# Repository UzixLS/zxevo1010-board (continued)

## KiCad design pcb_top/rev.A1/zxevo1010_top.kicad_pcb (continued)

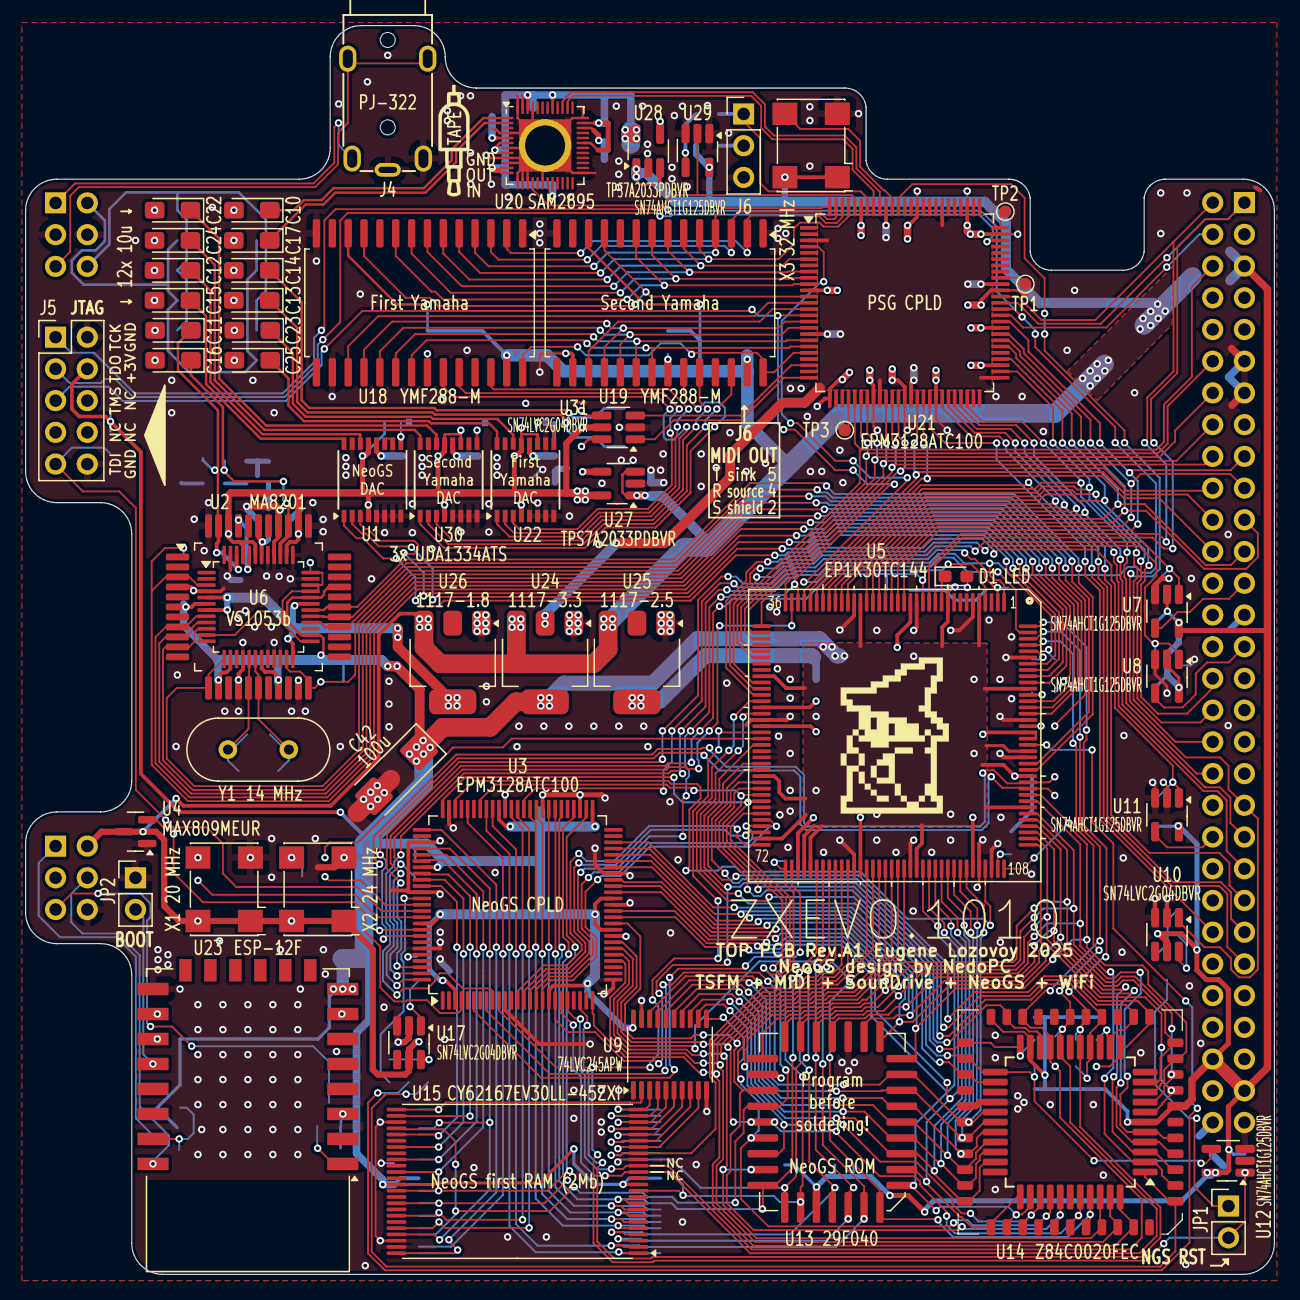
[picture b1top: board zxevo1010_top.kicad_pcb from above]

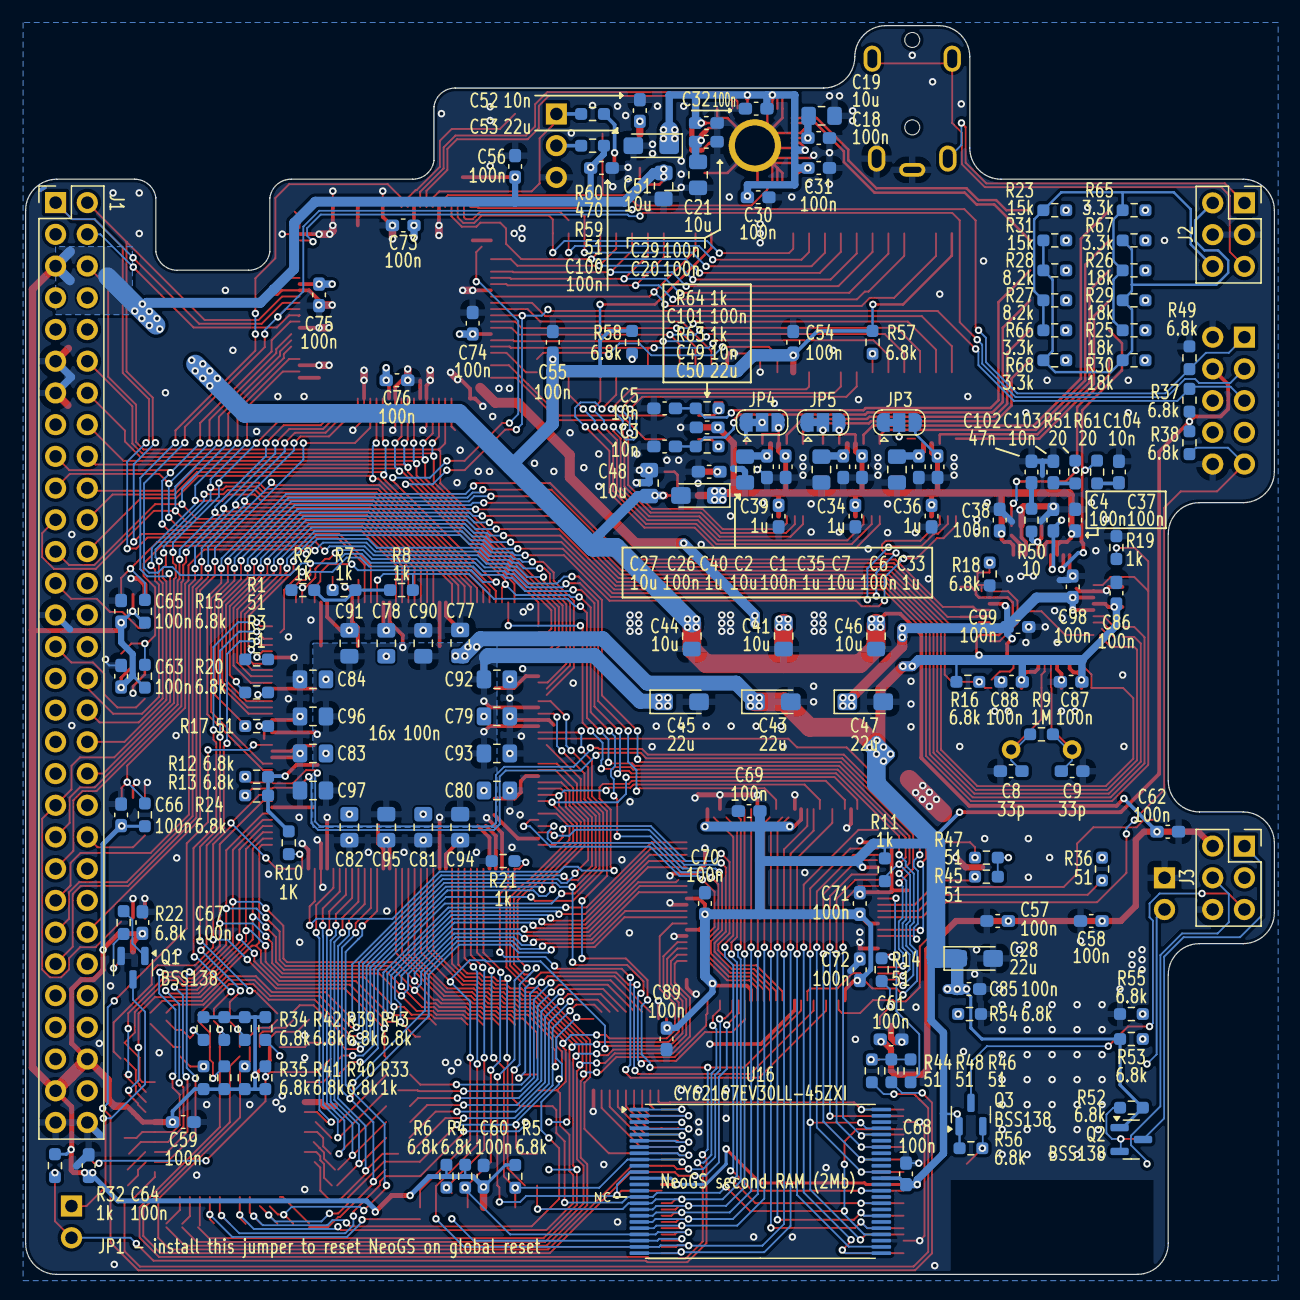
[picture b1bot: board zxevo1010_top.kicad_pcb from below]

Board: 2 copper layers, 100.0 x 100.0 mm, 224 parts (168 on the bottom side), 251 nets.
